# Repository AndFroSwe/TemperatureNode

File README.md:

# Temperature Node
Distributed node that runs on battery and sends temperature wirelessly via 
Bluetooth. 

## Requirements
These are the requirements that the unit should fulfill.

1. Shall run on battery power.
2. Shall work for at least two weeks.
3. Shall speak wirelessly via bluetooth.
4. Shall tell temperature with a simple serial message.

## Needed modules
These are the abstract units needed.

1. Power supply unit.
2. Microprocessor.
3. Temperature sensor.
4. Bluetooth module.

## Hardware
This is the hardware available.

1. DC-DC switching regulator MC33063 ([Datasheet](http://www.farnell.com/datasheets/1862376.pdf?_ga=1.207761298.1201322026.1473664451)).
2. Atmel Atmega 328P ([Datasheet](http://www.atmel.com/images/Atmel-8271-8-bit-AVR-Microcontroller-ATmega48A-48PA-88A-88PA-168A-168PA-328-328P_datasheet_Complete.pdf)).
3. Temperature and humidity sensor LMT84 ([Datasheet](http://www.ti.com/lit/ds/symlink/lmt84.pdf)).
4. HC-05 bluetooth module ([Datasheet](http://elecfreaks.com/store/download/datasheet/Bluetooth/HC-0305%20serail%20module%20AT%20commamd%20set%20201104%20revised.pdf)).

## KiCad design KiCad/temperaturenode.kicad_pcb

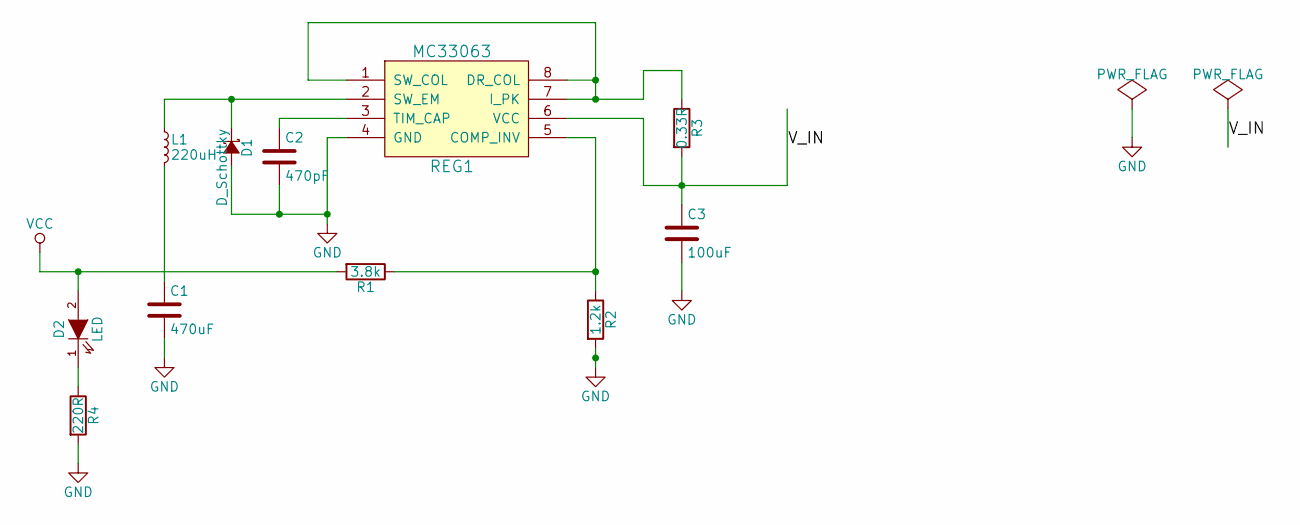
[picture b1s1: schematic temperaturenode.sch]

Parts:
C1: 470uF; C_Disc_D6_P5
C2: 470pF; C_Disc_D6_P5
C3: 100uF; C_Disc_D6_P5
D1: D_Schottky; Diode_DO-41_SOD81_Horizontal_RM10
D2: LED; LED-3MM
L1: 220uH; Choke_Toroid_horizontal_Diameter9mm_Amidon-T30
R1: 3.8k; Resistor_Vertical_RM5mm
R2: 1.2k; Resistor_Vertical_RM5mm
R3: 0.33R; Resistor_Vertical_RM5mm
R4: 220R; Resistor_Vertical_RM5mm
REG1: MC33063; DIP-8_W7.62mm

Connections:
/V_IN: C3.1, R3.2, REG1.6 (VCC)
GND: C1.2, C2.2, C3.2, D1.2 (A), R2.2, R4.2, REG1.4 (GND)
unnamed: C1.1, L1.2
unnamed: C2.1, REG1.3 (TIM_CAP)
unnamed: D1.1 (K), L1.1, REG1.2 (SW_EM)
unnamed: D2.1 (K), R4.1
unnamed: R1.1, R2.1, REG1.5 (COMP_INV)
unnamed: R3.1, REG1.1 (SW_COL), REG1.7 (I_PK), REG1.8 (DR_COL)
VCC: D2.2 (A), R1.2

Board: 2 copper layers, 11 parts (0 on the bottom side), 9 nets, no tracks yet.

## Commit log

2016-09-29 Initial commit. Added a readme and a gitignore.
2016-09-30 Added the voltage regulator on the eeschema
2016-09-30 Made a standalone pdu to test
